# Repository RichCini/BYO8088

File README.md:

# BYO8088
This is a modern implementation of the 8088 minimum mode SBC based on the one from Walter Fuller
as used in his book "Build Your Own Computer".

## Introduction
The orignal design as built in the book appears to have been done on a breadboard, so I took
the basic design and implemented it (partially) in an ECB (100mm x 160mm) format to take
advantage (ultimately) of various peripherals available in the Retrobrew Computer board
series.

## How is this version different?
As currently drawn, my reimplementation makes the following changes:

- Adds three 73LS373 drivers for the address bus in the event I want to expose those to
  the ECB connector (which right now is only for power).

- Removed the ADC0808 analog-to-digital converter.

- Used only one 82C55 I/O chip.

- Removed the RS-232 level shifters in favor of a header for a USB dongle.

- Added jumpers for the EPROM to allow for a flash-equivalent chip.

## Testing
As of now, this design is untested but I don't see why it wouldn't work.

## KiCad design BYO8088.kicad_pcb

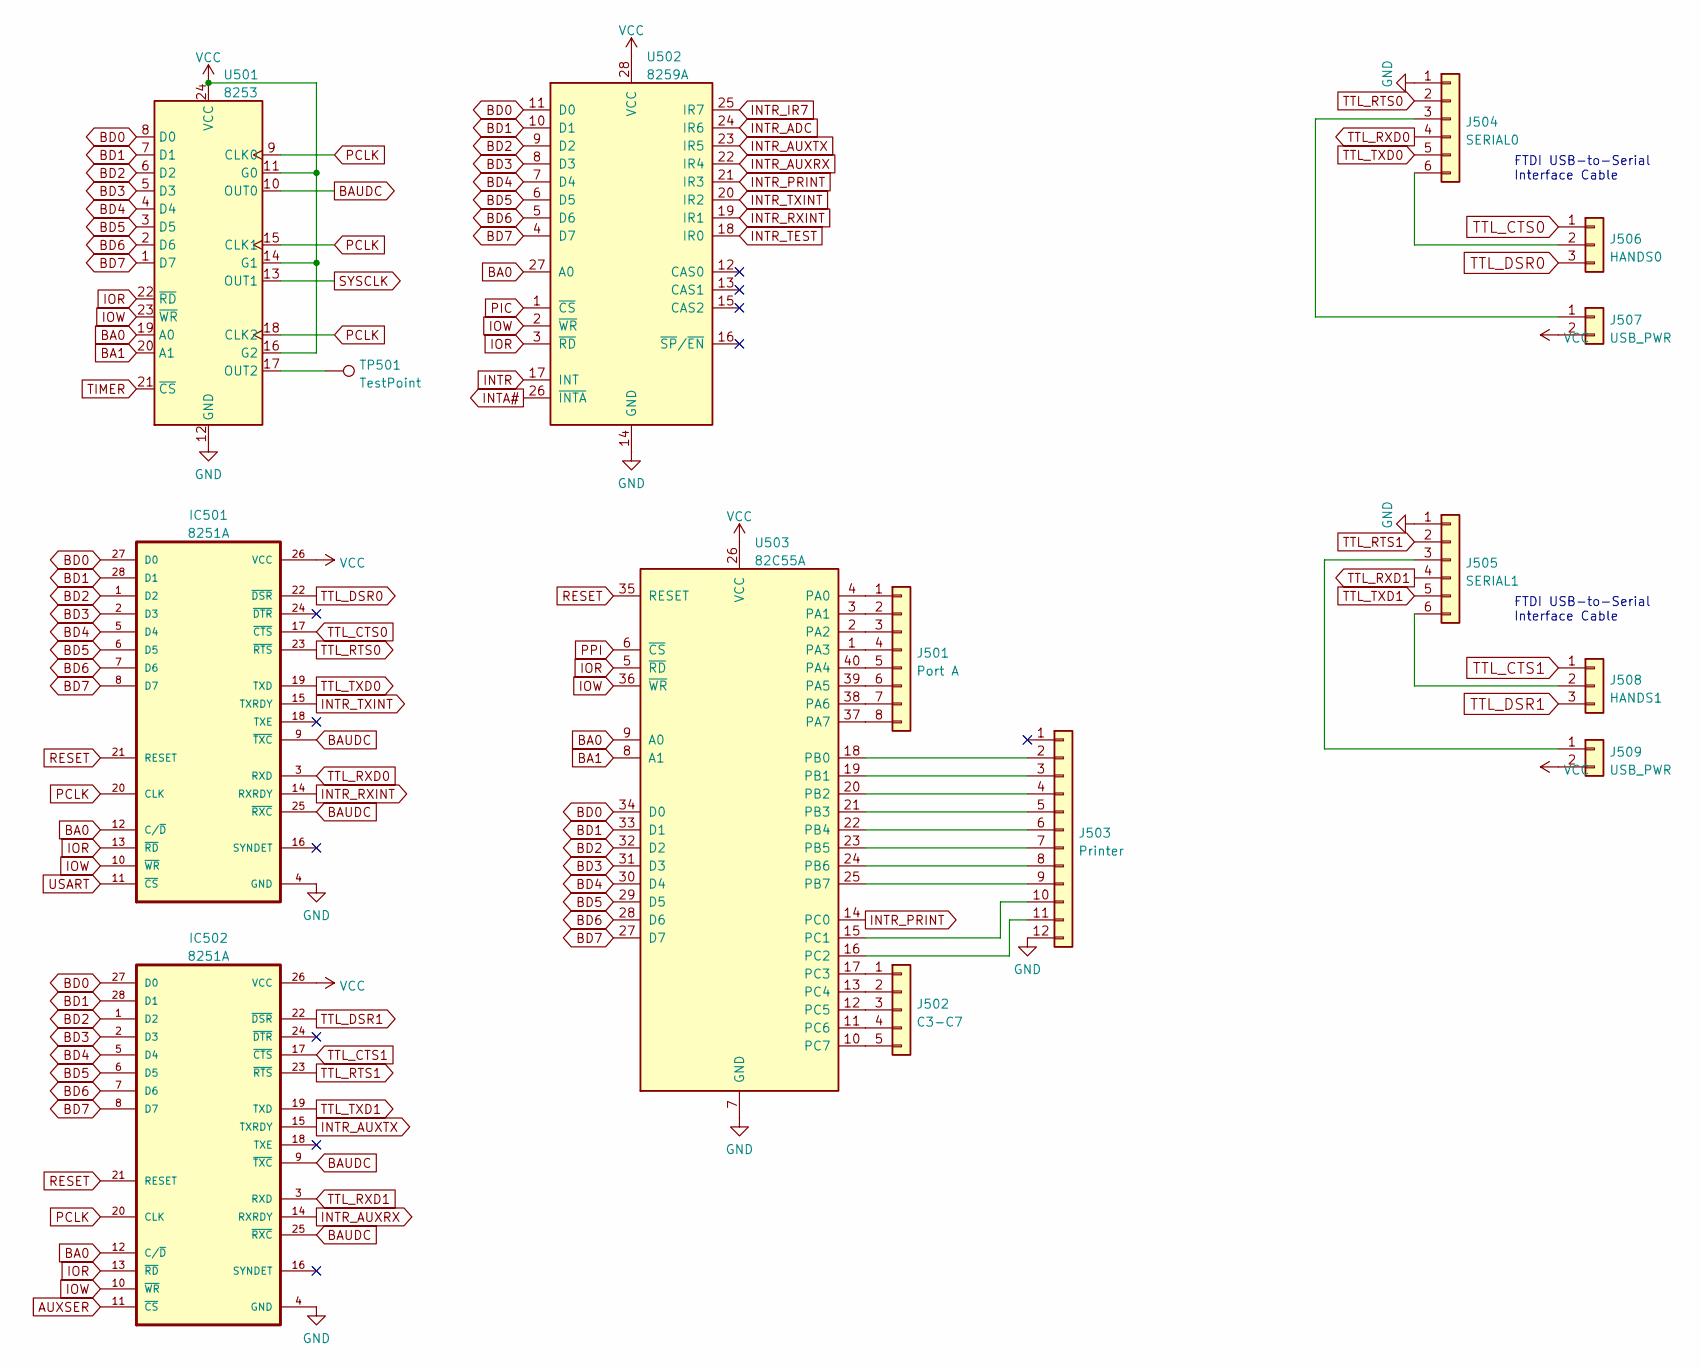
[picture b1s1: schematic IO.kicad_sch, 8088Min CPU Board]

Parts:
IC501, IC502: 8251A; DIP-28_W15.24mm
J501: Port A; PinHeader_1x08_P2.54mm_Vertical
J502: C3-C7; PinHeader_1x05_P2.54mm_Vertical
J503: Printer; PinHeader_1x12_P2.54mm_Vertical
J504: SERIAL0; PinHeader_1x06_P2.54mm_Vertical
J505: SERIAL1; PinHeader_1x06_P2.54mm_Vertical
J506: HANDS0; PinHeader_1x03_P2.54mm_Vertical
J507, J509: USB_PWR; PinHeader_1x02_P2.54mm_Vertical
J508: HANDS1; PinHeader_1x03_P2.54mm_Vertical
TP501: TestPoint; TestPoint_THTPad_1.5x1.5mm_Drill0.7mm
U501: 8253; DIP-24_W15.24mm
U502: 8259A; DIP-28_W15.24mm
U503: 82C55A; DIP-40_W15.24mm

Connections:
AUXSER: IC502.11 (~CS); also elsewhere on the board
BA0: IC501.12 (C/~D), IC502.12 (C/~D), U501.19 (A0), U502.27 (A0), U503.9 (A0); also elsewhere on the board
BA1: U501.20 (A1), U503.8 (A1); also elsewhere on the board
BAUDC: IC501.9 (~TXC), IC501.25 (~RXC), IC502.9 (~TXC), IC502.25 (~RXC), U501.10 (OUT0)
BD0: IC501.27 (D0), IC502.27 (D0), U501.8 (D0), U502.11 (D0), U503.34 (D0); also elsewhere on the board
BD1: IC501.28 (D1), IC502.28 (D1), U501.7 (D1), U502.10 (D1), U503.33 (D1); also elsewhere on the board
BD2: IC501.1 (D2), IC502.1 (D2), U501.6 (D2), U502.9 (D2), U503.32 (D2); also elsewhere on the board
BD3: IC501.2 (D3), IC502.2 (D3), U501.5 (D3), U502.8 (D3), U503.31 (D3); also elsewhere on the board
BD4: IC501.5 (D4), IC502.5 (D4), U501.4 (D4), U502.7 (D4), U503.30 (D4); also elsewhere on the board
BD5: IC501.6 (D5), IC502.6 (D5), U501.3 (D5), U502.6 (D5), U503.29 (D5); also elsewhere on the board
BD6: IC501.7 (D6), IC502.7 (D6), U501.2 (D6), U502.5 (D6), U503.28 (D6); also elsewhere on the board
BD7: IC501.8 (D7), IC502.8 (D7), U501.1 (D7), U502.4 (D7), U503.27 (D7); also elsewhere on the board
GND: IC501.4 (GND), IC502.4 (GND), J503.12, J504.1, J505.1, U501.12 (GND), U502.14 (GND), U503.7 (GND); also elsewhere on the board
INTA#: U502.26 (~INTA); also elsewhere on the board
INTR: U502.17 (INT); also elsewhere on the board
INTR_ADC: U502.24 (IR6)
INTR_AUXRX: IC502.14 (RXRDY), U502.22 (IR4)
INTR_AUXTX: IC502.15 (TXRDY), U502.23 (IR5)
INTR_IR7: U502.25 (IR7)
INTR_PRINT: U502.21 (IR3), U503.14 (PC0)
INTR_RXINT: IC501.14 (RXRDY), U502.19 (IR1)
INTR_TEST: U502.18 (IR0)
INTR_TXINT: IC501.15 (TXRDY), U502.20 (IR2)
IOR: IC501.13 (~RD), IC502.13 (~RD), U501.22 (~RD), U502.3 (~RD), U503.5 (~RD); also elsewhere on the board
IOW: IC501.10 (~WR), IC502.10 (~WR), U501.23 (~WR), U502.2 (~WR), U503.36 (~WR); also elsewhere on the board
unnamed: J501.1, U503.4 (PA0)
unnamed: J501.2, U503.3 (PA1)
unnamed: J501.3, U503.2 (PA2)
unnamed: J501.4, U503.1 (PA3)
unnamed: J501.5, U503.40 (PA4)
unnamed: J501.6, U503.39 (PA5)
unnamed: J501.7, U503.38 (PA6)
unnamed: J501.8, U503.37 (PA7)
unnamed: J502.1, U503.17 (PC3)
unnamed: J502.2, U503.13 (PC4)
unnamed: J502.3, U503.12 (PC5)
unnamed: J502.4, U503.11 (PC6)
unnamed: J502.5, U503.10 (PC7)
unnamed: J503.2, U503.18 (PB0)
unnamed: J503.3, U503.19 (PB1)
unnamed: J503.4, U503.20 (PB2)
unnamed: J503.5, U503.21 (PB3)
unnamed: J503.6, U503.22 (PB4)
unnamed: J503.7, U503.23 (PB5)
unnamed: J503.8, U503.24 (PB6)
unnamed: J503.9, U503.25 (PB7)
unnamed: J503.10, U503.15 (PC1)
unnamed: J503.11, U503.16 (PC2)
unnamed: J504.3, J507.1
unnamed: J504.6, J506.2
unnamed: J505.3, J509.1
unnamed: J505.6, J508.2
unnamed: TP501.1, U501.17 (OUT2)
PCLK: IC501.20 (CLK), IC502.20 (CLK), U501.9 (CLK0), U501.15 (CLK1), U501.18 (CLK2); also elsewhere on the board
PIC: U502.1 (~CS); also elsewhere on the board
PPI: U503.6 (~CS); also elsewhere on the board
RESET: IC501.21 (RESET), IC502.21 (RESET), U503.35 (RESET); also elsewhere on the board
SYSCLK: U501.13 (OUT1); also elsewhere on the board
TIMER: U501.21 (~CS); also elsewhere on the board
TTL_CTS0: IC501.17 (~CTS), J506.1
TTL_CTS1: IC502.17 (~CTS), J508.1
TTL_DSR0: IC501.22 (~DSR), J506.3
TTL_DSR1: IC502.22 (~DSR), J508.3
TTL_RTS0: IC501.23 (~RTS), J504.2
TTL_RTS1: IC502.23 (~RTS), J505.2
TTL_RXD0: IC501.3 (RXD), J504.4
TTL_RXD1: IC502.3 (RXD), J505.4
TTL_TXD0: IC501.19 (TXD), J504.5
TTL_TXD1: IC502.19 (TXD), J505.5
USART: IC501.11 (~CS); also elsewhere on the board
VCC: IC501.26 (VCC), IC502.26 (VCC), J507.2, J509.2, U501.11 (G0), U501.14 (G1), U501.16 (G2), U501.24 (VCC), U502.28 (VCC), U503.26 (VCC); also elsewhere on the board

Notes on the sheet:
FTDI USB-to-Serial Interface Cable

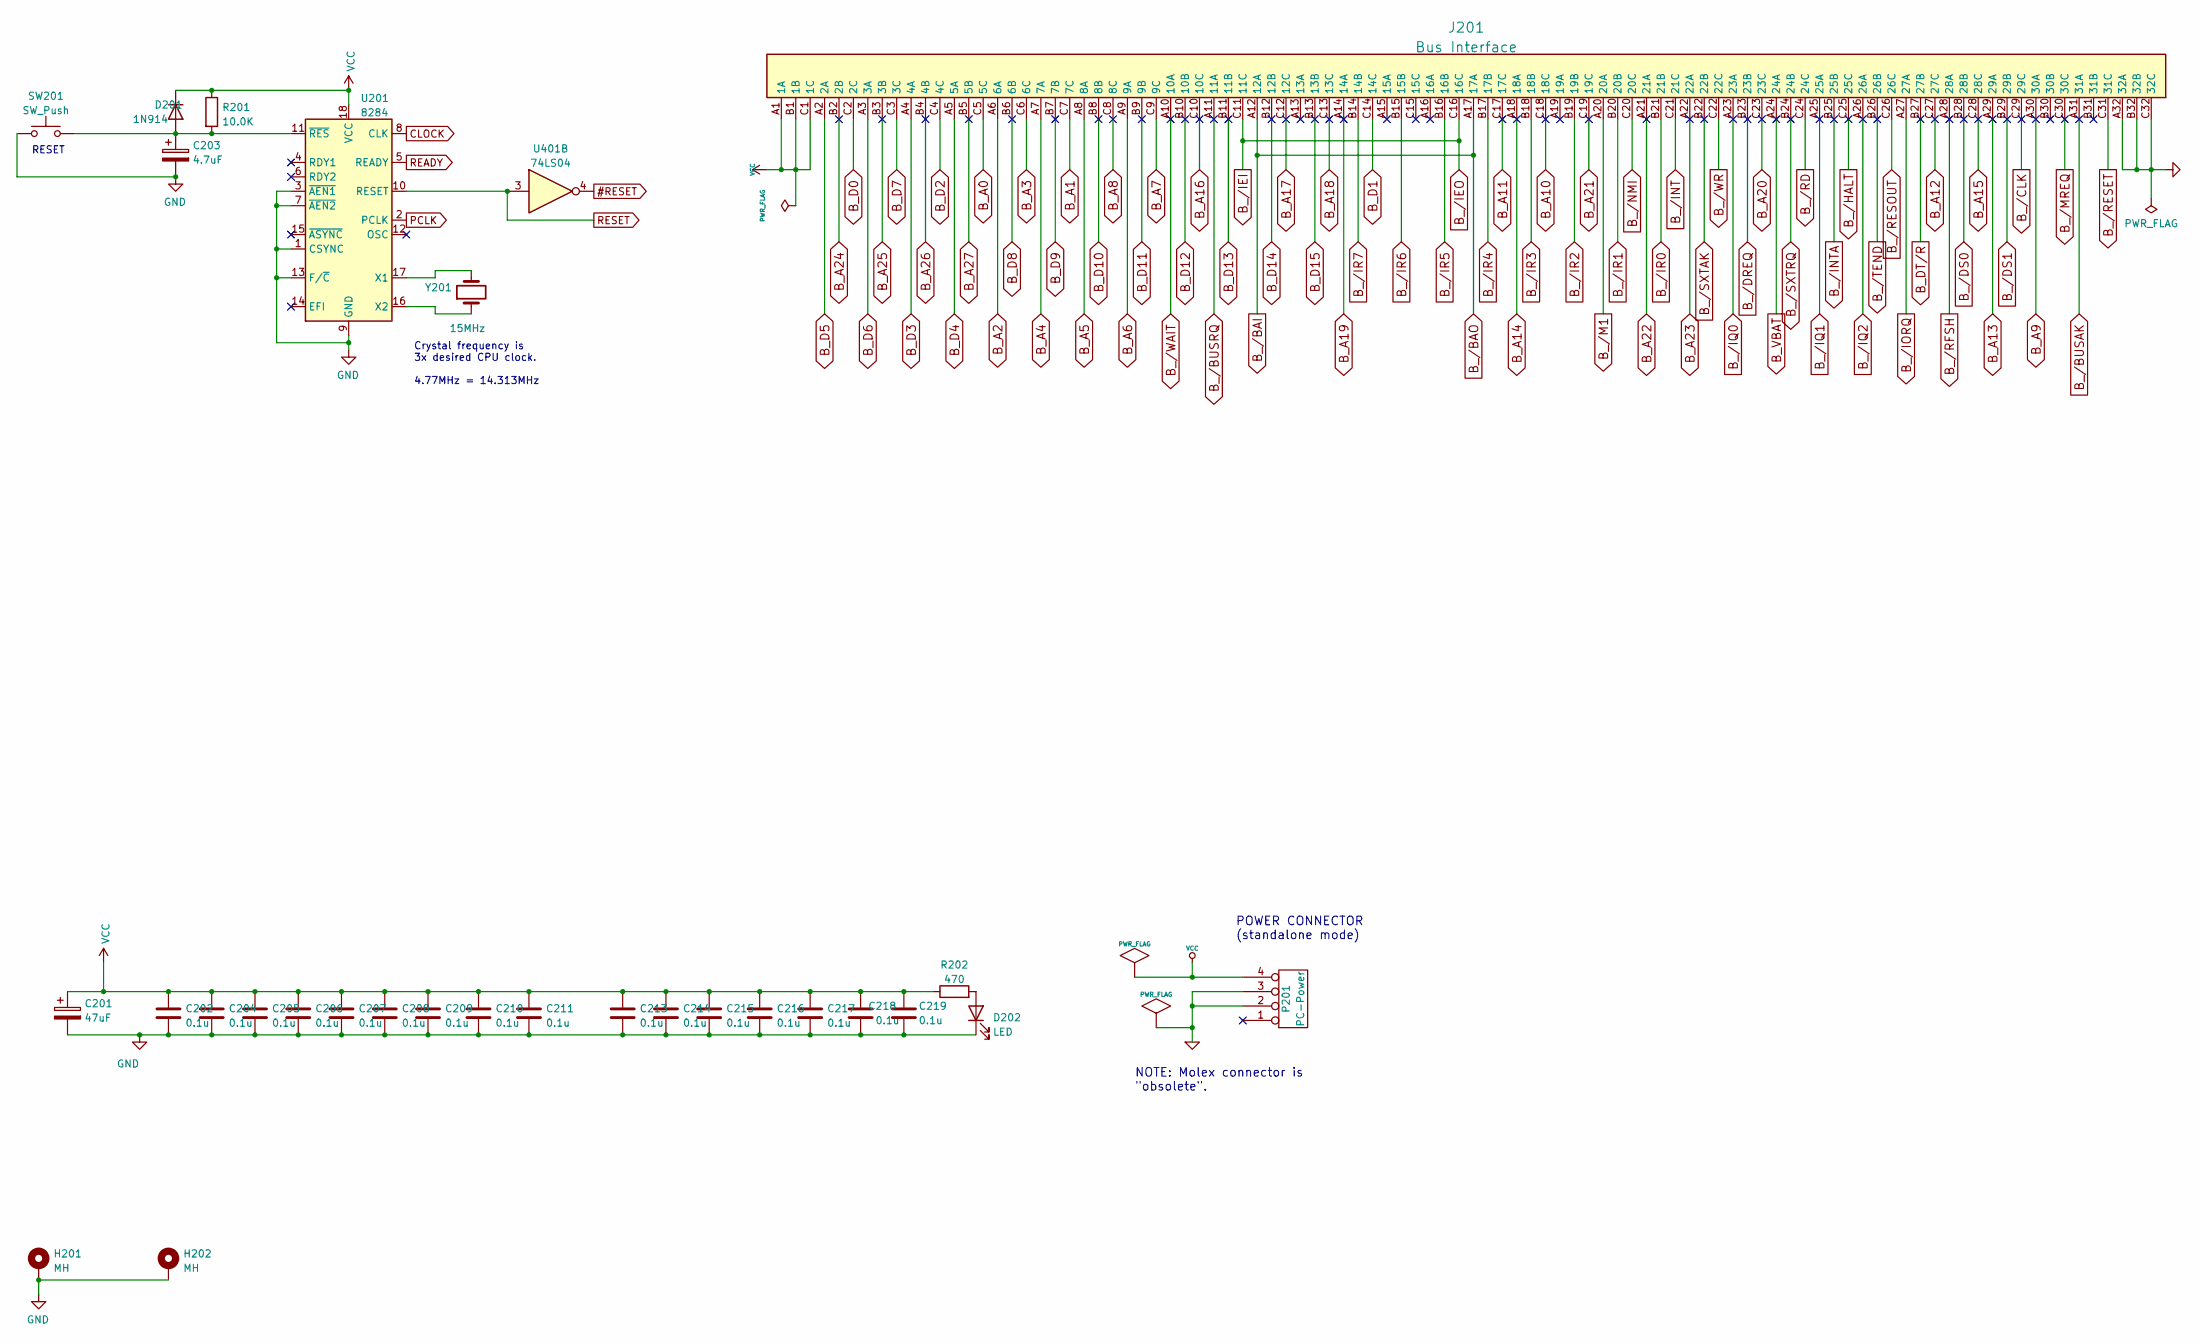
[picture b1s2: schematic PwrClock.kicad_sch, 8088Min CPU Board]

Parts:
C201: 47uF; CP_Radial_D4.0mm_P2.00mm
C202, C204, C205, C206, C207, C208, C209, C210, C211, C213, C214, C215, C216, C217, C218, C219: 0.1u; C_Disc_D7.5mm_W2.5mm_P5.00mm
C203: 4.7uF; CP_Radial_D4.0mm_P2.00mm
D201: 1N914; D_A-405_P7.62mm_Horizontal
D202: LED; LED_D3.0mm
H201, H202: MH; MountingHole_2.2mm_M2_Pad
J201: Bus Interface; C96ABCM-RA
P201: PC-Power
R201: 10.0K; R_Axial_DIN0207_L6.3mm_D2.5mm_P7.62mm_Horizontal
R202: 470; R_Axial_DIN0207_L6.3mm_D2.5mm_P7.62mm_Horizontal
SW201: SW_Push; SW_Tactile_SPST_Angled_PTS645Vx31-2LFS
U201: 8284; DIP-18_W7.62mm
U401: 74LS04; DIP-14_W7.62mm_Socket
Y201: 15MHz; Crystal_HC49-U_Vertical

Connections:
#RESET: U401.4
B_A0: J201.C5 (5C)
B_A1: J201.C7 (7C)
B_A2: J201.A6 (6A)
B_A3: J201.C6 (6C)
B_A4: J201.A7 (7A)
B_A5: J201.A8 (8A)
B_A6: J201.A9 (9A)
B_A7: J201.C9 (9C)
B_A8: J201.C8 (8C)
B_A9: J201.A30 (30A)
B_A10: J201.C18 (18C)
B_A11: J201.C17 (17C)
B_A12: J201.C27 (27C)
B_A13: J201.A29 (29A)
B_A14: J201.A18 (18A)
B_A15: J201.C28 (28C)
B_A16: J201.C10 (10C)
B_A17: J201.C12 (12C)
B_A18: J201.C13 (13C)
B_A19: J201.A14 (14A)
B_A20: J201.C23 (23C)
B_A21: J201.C19 (19C)
B_A22: J201.A21 (21A)
B_A23: J201.A22 (22A)
B_A24: J201.B2 (2B)
B_A25: J201.B3 (3B)
B_A26: J201.B4 (4B)
B_A27: J201.B5 (5B)
B_D0: J201.C2 (2C)
B_D1: J201.C14 (14C)
B_D2: J201.C4 (4C)
B_D3: J201.A4 (4A)
B_D4: J201.A5 (5A)
B_D5: J201.A2 (2A)
B_D6: J201.A3 (3A)
B_D7: J201.C3 (3C)
B_D8: J201.B6 (6B)
B_D9: J201.B7 (7B)
B_D10: J201.B8 (8B)
B_D11: J201.B9 (9B)
B_D12: J201.B10 (10B)
B_D13: J201.B11 (11B)
B_D14: J201.B12 (12B)
B_D15: J201.B13 (13B)
B_DT/R: J201.B27 (27B)
B_VBAT: J201.A24 (24A)
B_/BAI: J201.A12 (12A), J201.A17 (17A)
B_/BUSAK: J201.A31 (31A)
B_/BUSRQ: J201.A11 (11A)
B_/CLK: J201.C29 (29C)
B_/DREQ: J201.B23 (23B)
B_/DS0: J201.B28 (28B)
B_/DS1: J201.B29 (29B)
B_/HALT: J201.C25 (25C)
B_/IEI: J201.C11 (11C), J201.C16 (16C)
B_/INT: J201.C21 (21C)
B_/INTA: J201.B25 (25B)
B_/IORQ: J201.A27 (27A)
B_/IQ0: J201.A23 (23A)
B_/IQ1: J201.A25 (25A)
B_/IQ2: J201.A26 (26A)
B_/IR0: J201.B21 (21B)
B_/IR1: J201.B20 (20B)
B_/IR2: J201.B19 (19B)
B_/IR3: J201.B18 (18B)
B_/IR4: J201.B17 (17B)
B_/IR5: J201.B16 (16B)
B_/IR6: J201.B15 (15B)
B_/IR7: J201.B14 (14B)
B_/M1: J201.A20 (20A)
B_/MREQ: J201.C30 (30C)
B_/NMI: J201.C20 (20C)
B_/RD: J201.C24 (24C)
B_/RESET: J201.C31 (31C)
B_/RESOUT: J201.C26 (26C)
B_/RFSH: J201.A28 (28A)
B_/SXTAK: J201.B22 (22B)
B_/SXTRQ: J201.B24 (24B)
B_/TEND: J201.B26 (26B)
B_/WAIT: J201.A10 (10A)
B_/WR: J201.C22 (22C)
CLOCK: U201.8 (CLK); also elsewhere on the board
GND: C201.2, C202.2, C203.2, C204.2, C205.2, C206.2, C207.2, C208.2, C209.2, C210.2, C211.2, C213.2, C214.2, C215.2, C216.2, C217.2, C218.2, C219.2, D202.1 (K), H201.1, H202.1, J201.A32 (32A), J201.B32 (32B), J201.C32 (32C), J201.HOLE, P201.2, P201.3, SW201.1, U201.1 (CSYNC), U201.3 (~AEN1), U201.7 (~AEN2), U201.9 (GND), U201.13 (F/~C); also elsewhere on the board
unnamed: C203.1, D201.2 (A), R201.2, SW201.2, U201.11 (~RES)
unnamed: D202.2 (A), R202.2
unnamed: U201.16 (X2), Y201.1
unnamed: U201.17 (X1), Y201.2
PCLK: U201.2 (PCLK); also elsewhere on the board
READY: U201.5 (READY); also elsewhere on the board
RESET: U201.10 (RESET), U401.3; also elsewhere on the board
VCC: C201.1, C202.1, C204.1, C205.1, C206.1, C207.1, C208.1, C209.1, C210.1, C211.1, C213.1, C214.1, C215.1, C216.1, C217.1, C218.1, C219.1, D201.1 (K), J201.A1 (1A), J201.B1 (1B), J201.C1 (1C), P201.4, R201.1, R202.1, U201.18 (VCC); also elsewhere on the board

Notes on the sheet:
NOTE: Molex connector is "obsolete".
POWER CONNECTOR (standalone mode)
RESET
Crystal frequency is 3x desired CPU clock. 4.77MHz = 14.313MHz

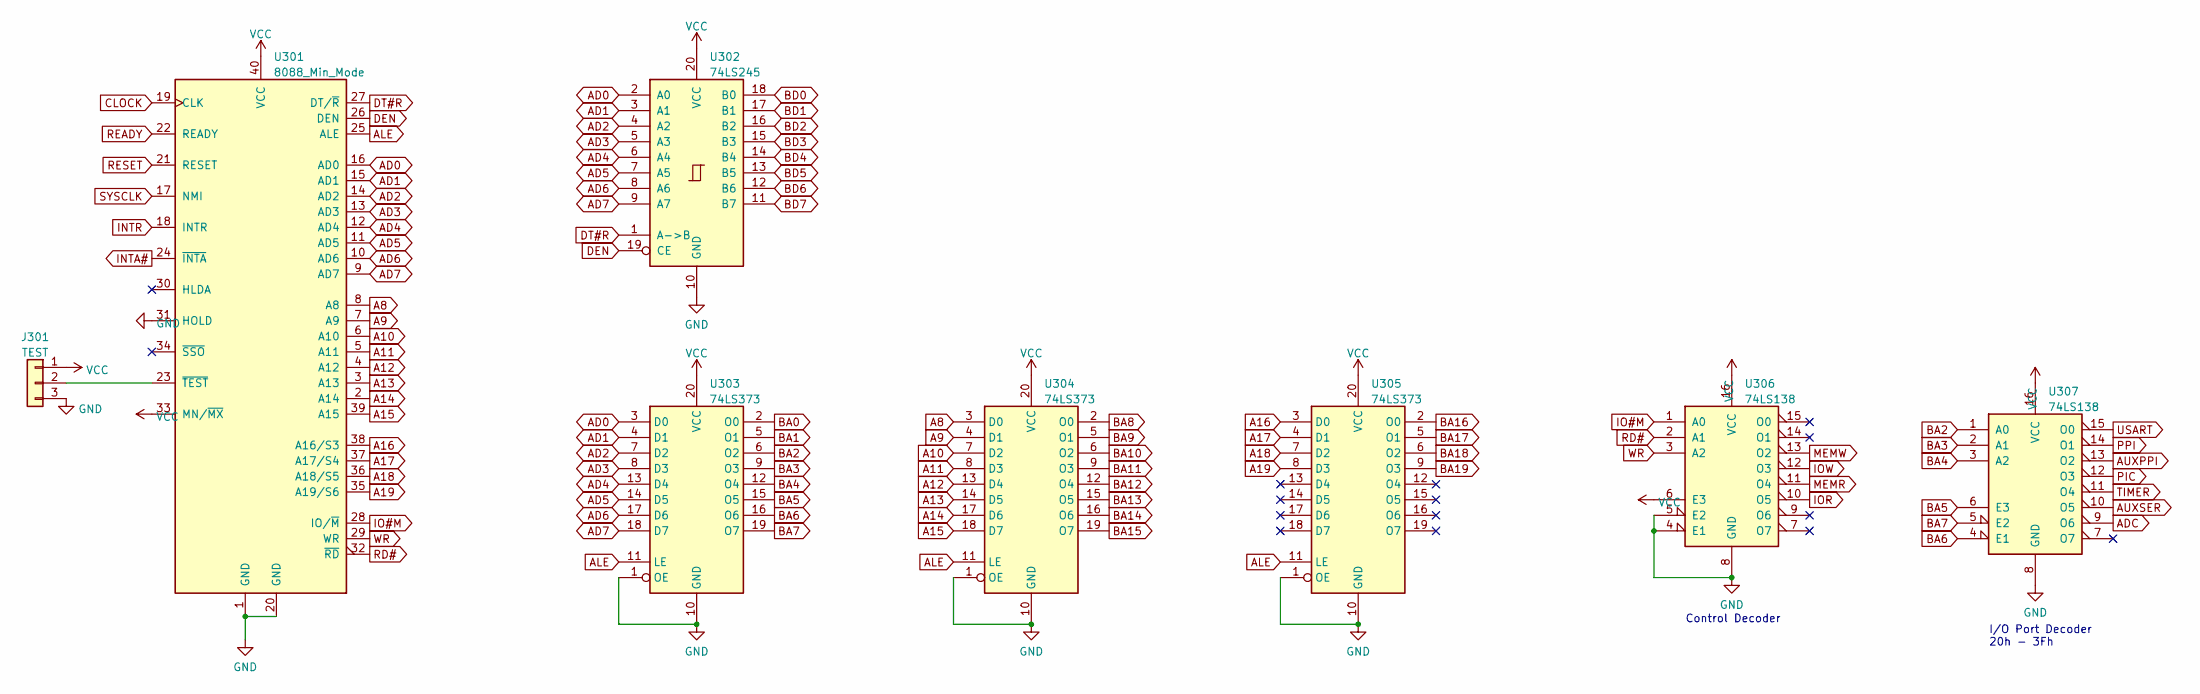
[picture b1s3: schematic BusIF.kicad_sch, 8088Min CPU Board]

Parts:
J301: TEST; PinHeader_1x03_P2.54mm_Vertical
U301: 8088_Min_Mode; DIP-40_W15.24mm
U302: 74LS245; DIP-20_W7.62mm_Socket
U303, U304, U305: 74LS373; DIP-20_W7.62mm_Socket
U306, U307: 74LS138; DIP-16_W7.62mm_Socket

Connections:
A8: U301.8 (A8), U304.3 (D0)
A9: U301.7 (A9), U304.4 (D1)
A10: U301.6 (A10), U304.7 (D2)
A11: U301.5 (A11), U304.8 (D3)
A12: U301.4 (A12), U304.13 (D4)
A13: U301.3 (A13), U304.14 (D5)
A14: U301.2 (A14), U304.17 (D6)
A15: U301.39 (A15), U304.18 (D7)
A16: U301.38 (A16/S3), U305.3 (D0)
A17: U301.37 (A17/S4), U305.4 (D1)
A18: U301.36 (A18/S5), U305.7 (D2)
A19: U301.35 (A19/S6), U305.8 (D3)
AD0: U301.16 (AD0), U302.2 (A0), U303.3 (D0)
AD1: U301.15 (AD1), U302.3 (A1), U303.4 (D1)
AD2: U301.14 (AD2), U302.4 (A2), U303.7 (D2)
AD3: U301.13 (AD3), U302.5 (A3), U303.8 (D3)
AD4: U301.12 (AD4), U302.6 (A4), U303.13 (D4)
AD5: U301.11 (AD5), U302.7 (A5), U303.14 (D5)
AD6: U301.10 (AD6), U302.8 (A6), U303.17 (D6)
AD7: U301.9 (AD7), U302.9 (A7), U303.18 (D7)
ADC: U307.9 (O6)
ALE: U301.25 (ALE), U303.11 (LE), U304.11 (LE), U305.11 (LE)
AUXPPI: U307.13 (O2)
AUXSER: U307.10 (O5); also elsewhere on the board
BA0: U303.2 (O0); also elsewhere on the board
BA1: U303.5 (O1); also elsewhere on the board
BA2: U303.6 (O2), U307.1 (A0); also elsewhere on the board
BA3: U303.9 (O3), U307.2 (A1); also elsewhere on the board
BA4: U303.12 (O4), U307.3 (A2); also elsewhere on the board
BA5: U303.15 (O5), U307.6 (E3); also elsewhere on the board
BA6: U303.16 (O6), U307.4 (E1); also elsewhere on the board
BA7: U303.19 (O7), U307.5 (E2); also elsewhere on the board
BA8: U304.2 (O0); also elsewhere on the board
BA9: U304.5 (O1); also elsewhere on the board
BA10: U304.6 (O2); also elsewhere on the board
BA11: U304.9 (O3); also elsewhere on the board
BA12: U304.12 (O4); also elsewhere on the board
BA13: U304.15 (O5); also elsewhere on the board
BA14: U304.16 (O6); also elsewhere on the board
BA15: U304.19 (O7); also elsewhere on the board
BA16: U305.2 (O0)
BA17: U305.5 (O1)
BA18: U305.6 (O2)
BA19: U305.9 (O3)
BD0: U302.18 (B0); also elsewhere on the board
BD1: U302.17 (B1); also elsewhere on the board
BD2: U302.16 (B2); also elsewhere on the board
BD3: U302.15 (B3); also elsewhere on the board
BD4: U302.14 (B4); also elsewhere on the board
BD5: U302.13 (B5); also elsewhere on the board
BD6: U302.12 (B6); also elsewhere on the board
BD7: U302.11 (B7); also elsewhere on the board
CLOCK: U301.19 (CLK); also elsewhere on the board
DEN: U301.26 (DEN), U302.19 (CE)
DT#R: U301.27 (DT/~R), U302.1 (A->B)
GND: J301.3, U301.1 (GND), U301.20 (GND), U301.31 (HOLD), U302.10 (GND), U303.1 (OE), U303.10 (GND), U304.1 (OE), U304.10 (GND), U305.1 (OE), U305.10 (GND), U306.4 (E1), U306.5 (E2), U306.8 (GND), U307.8 (GND); also elsewhere on the board
INTA#: U301.24 (~INTA); also elsewhere on the board
INTR: U301.18 (INTR); also elsewhere on the board
IO#M: U301.28 (IO/~M), U306.1 (A0)
IOR: U306.10 (O5); also elsewhere on the board
IOW: U306.12 (O3); also elsewhere on the board
MEMR: U306.11 (O4); also elsewhere on the board
MEMW: U306.13 (O2); also elsewhere on the board
unnamed: J301.2, U301.23 (~TEST)
PIC: U307.12 (O3); also elsewhere on the board
PPI: U307.14 (O1); also elsewhere on the board
RD#: U301.32 (~RD), U306.2 (A1)
READY: U301.22 (READY); also elsewhere on the board
RESET: U301.21 (RESET); also elsewhere on the board
SYSCLK: U301.17 (NMI); also elsewhere on the board
TIMER: U307.11 (O4); also elsewhere on the board
USART: U307.15 (O0); also elsewhere on the board
VCC: J301.1, U301.33 (MN/~MX), U301.40 (VCC), U302.20 (VCC), U303.20 (VCC), U304.20 (VCC), U305.20 (VCC), U306.6 (E3), U306.16 (VCC), U307.16 (VCC); also elsewhere on the board
WR: U301.29 (WR), U306.3 (A2)

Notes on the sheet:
Control Decoder
I/O Port Decoder 20h - 3Fh

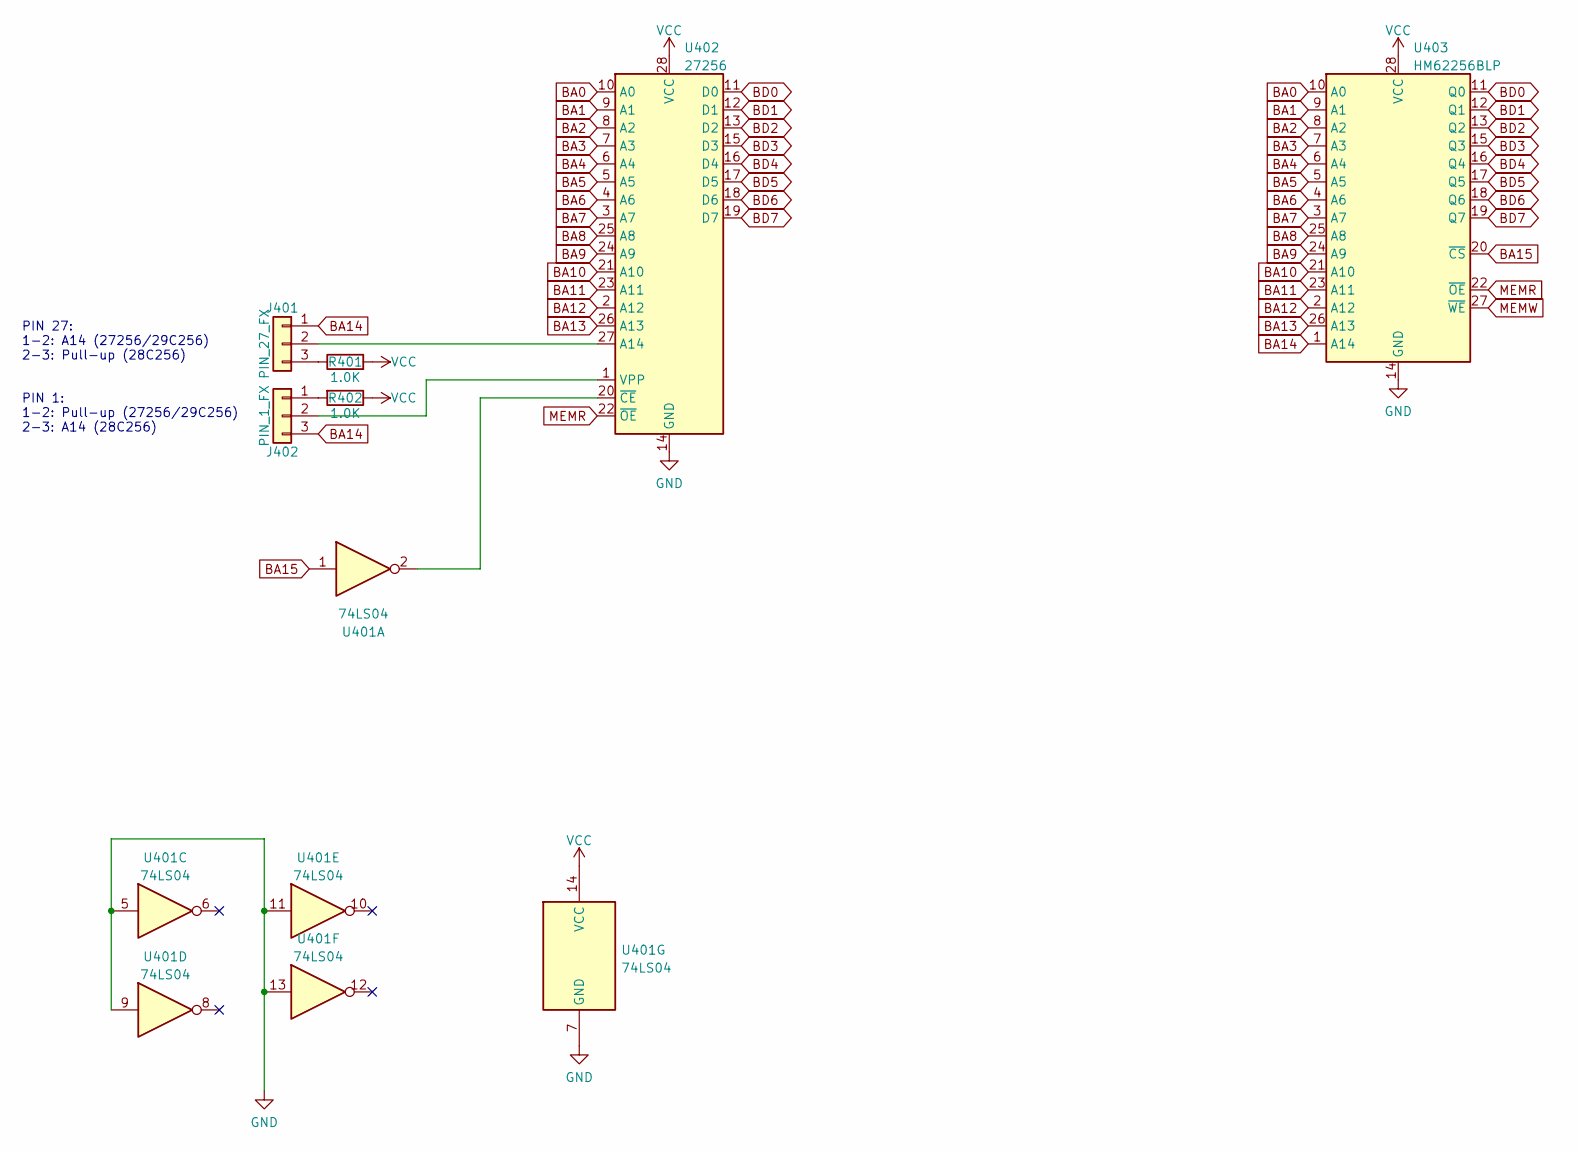
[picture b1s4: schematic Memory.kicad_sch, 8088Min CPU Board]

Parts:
J401: PIN_27_FX; PinHeader_1x03_P2.54mm_Vertical
J402: PIN_1_FX; PinHeader_1x03_P2.54mm_Vertical
R401, R402: 1.0K; R_Axial_DIN0207_L6.3mm_D2.5mm_P7.62mm_Horizontal
U401: 74LS04; DIP-14_W7.62mm_Socket
U402: 27256; DIP-28_W15.24mm
U403: HM62256BLP; DIP-28_W15.24mm

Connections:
BA0: U402.10 (A0), U403.10 (A0); also elsewhere on the board
BA1: U402.9 (A1), U403.9 (A1); also elsewhere on the board
BA2: U402.8 (A2), U403.8 (A2); also elsewhere on the board
BA3: U402.7 (A3), U403.7 (A3); also elsewhere on the board
BA4: U402.6 (A4), U403.6 (A4); also elsewhere on the board
BA5: U402.5 (A5), U403.5 (A5); also elsewhere on the board
BA6: U402.4 (A6), U403.4 (A6); also elsewhere on the board
BA7: U402.3 (A7), U403.3 (A7); also elsewhere on the board
BA8: U402.25 (A8), U403.25 (A8); also elsewhere on the board
BA9: U402.24 (A9), U403.24 (A9); also elsewhere on the board
BA10: U402.21 (A10), U403.21 (A10); also elsewhere on the board
BA11: U402.23 (A11), U403.23 (A11); also elsewhere on the board
BA12: U402.2 (A12), U403.2 (A12); also elsewhere on the board
BA13: U402.26 (A13), U403.26 (A13); also elsewhere on the board
BA14: J401.1, J402.3, U403.1 (A14); also elsewhere on the board
BA15: U401.1, U403.20 (~CS); also elsewhere on the board
BD0: U402.11 (D0), U403.11 (Q0); also elsewhere on the board
BD1: U402.12 (D1), U403.12 (Q1); also elsewhere on the board
BD2: U402.13 (D2), U403.13 (Q2); also elsewhere on the board
BD3: U402.15 (D3), U403.15 (Q3); also elsewhere on the board
BD4: U402.16 (D4), U403.16 (Q4); also elsewhere on the board
BD5: U402.17 (D5), U403.17 (Q5); also elsewhere on the board
BD6: U402.18 (D6), U403.18 (Q6); also elsewhere on the board
BD7: U402.19 (D7), U403.19 (Q7); also elsewhere on the board
GND: U401.5, U401.7 (GND), U401.9, U401.11, U401.13, U402.14 (GND), U403.14 (GND); also elsewhere on the board
MEMR: U402.22 (~OE), U403.22 (~OE); also elsewhere on the board
MEMW: U403.27 (~WE); also elsewhere on the board
unnamed: J401.2, U402.27 (A14)
unnamed: J401.3, R401.1
unnamed: J402.1, R402.2
unnamed: J402.2, U402.1 (VPP)
unnamed: U401.2, U402.20 (~CE)
VCC: R401.2, R402.1, U401.14 (VCC), U402.28 (VCC), U403.28 (VCC); also elsewhere on the board

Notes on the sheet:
PIN 27: 1-2: A14 (27256/29C256) 2-3: Pull-up (28C256)
PIN 1: 1-2: Pull-up (27256/29C256) 2-3: A14 (28C256)

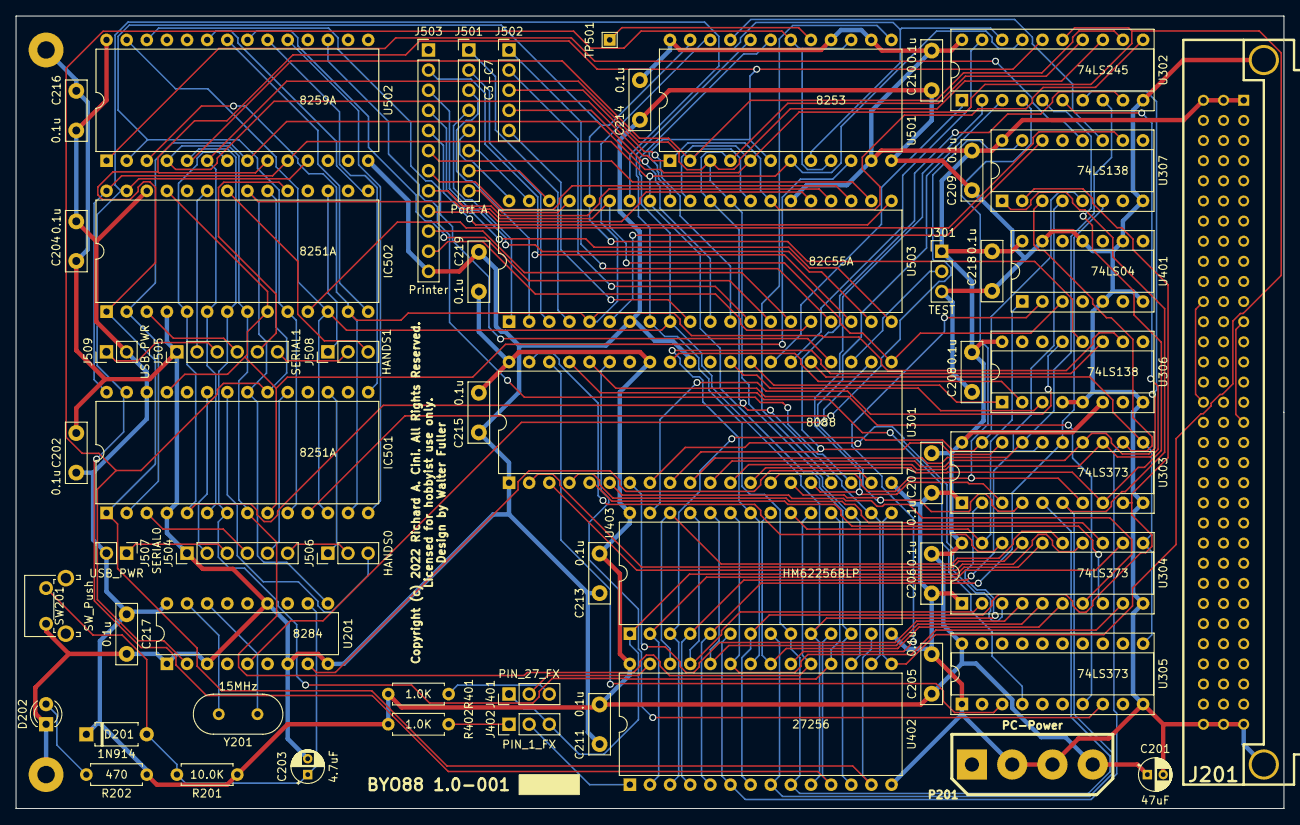
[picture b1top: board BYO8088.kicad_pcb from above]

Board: 2 copper layers, 160.0 x 100.0 mm, 59 parts (0 on the bottom side), 124 nets.

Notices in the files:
BYO8088.kicad_pcb:
Copyright (c) 2019 Richard Cini. All Rights reserved.
Copyright (c) 2022 Richard A. Cini. All Rights Reserved.
